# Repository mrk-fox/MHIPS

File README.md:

<h1 align="center">MHIPS</h1>
<div align="center">Modular Human Interface Panels System</div>
<br>
<div align="center">

</div>
<br>

<br> <br>
# Introduction
As controlling any type of craft with electronical components reqiring human intervention to function grows with the complexity of the craft and its tasks, I have decided to design a controlling system which is modular and uses near-aerospace-safety protocolls.

**Please pay attention to the fact that this project is still being developed. There is no "final solution" or such similar.**

## Functionality and goals

Every sucesfull project resembles a solution for a problem. Thus, the problem needs to be formulated before a solution is deigned. The problem that this project solves is the complexity of digital menus and the lack of haptic response in controlling anything with pure software.
My solution is a _modular, standartized panel system_ 
Hence, a ruleset was reqired to ensure the mulitcompatiability and extensiabiliy of this project.

### Why is it unique?
A central question in research, engineering and most other fields is "why has nobody done this before". Well, there are solutions to thes problem. Even one NASA provides in their GitHub repositories. But all of them are way to professional for amateur/non-professional use.

### Why did i make it?
Well, I'm planning on buiding an autonomous portable UAV someday. One day. Maybe. So these can be the GCC controls.

# Standartization

In this section we define a convention for the MHIPS (Modular Human Interface Panel System).
``` 
1. The abbreviation "MHIPS" stands for "Modular Human Interface Panel System".
      a. A panel is defined as a mounted and rigid resembly of multiple tiles, solving a user-defined task.
      b. A tile is defined as the smallest unit of the system. Any tile consists of the following components:
           b.1. A CAN-Capable read-write PCB as the BusPlate.
           b.2. A casing consisting of the front case and the backplate
           b.3. Input and output elements as Light Emitting Diodes, Buttons, Switches and more mounted into the front plate of the casing
      c. A rack is defined as the structure carrying and spacing the tiles.
2. The basic structure for a rack is a 5mm wide frame with the inner sizing of 50x50mm and a thickness of minimum 4mm. By fusing such frames togoether a rack is built. Each basic frame resembles the size of one unit (1U).
3. We define three levels of controll elements protection to ensure a dynamic range of application and environemntal adaptation.
      a. A level 3 tile is defined as a tile with no switch protection against accidental action.
      b. A level 2 tile is defined as a tile with sufficient control elements protection to ensure protection against accidental action. Only fully contacted switches (e.g.       ON-ON) are allowed.
      c. A level 1 tile is defined as a tile with maximal protection against accidental action. Double action is the minimum requirement. We split the level 1 category in the following subgroups:
            c.1. A level 1-S tile is definied as a tile meeting the basic level 1 requirements and the additional requirement of the maxiaml control element density of one control element per rack unit.
            c.2. A level 1-HV tile is definied as a tile meeting the basic level 1 requirements and additionally having the front tile face colored in a high visiability pattern (e.g. black and yellow stripes, 15mm wide at a 45° angle to the bottom plate of the tile) and having a maxiaml control element density of one control element per rack unit.
```
The given standartization is applied to all the racks and tiles in this current project.

# Example solution
In the following secion I will present my solution for the standartization and problem.

## BusPlate
The core piece of the work is the BusPlate resembling a PCB with the following features:

- RP2040 controller
- USB-C connectivity
- CAN Bus feature with MCP2515 controller
- Power and data over RJ45
- Decentralized computing capability on board

The following pictures are the front and back of the BusPlate PCB.

The following diagram shows the schematics for this PCB created in KiCad.

The following picures are the single PCB layers in the order "Front, In 1, In 2, Back"

## Assembly
Now, the assembly is rather simple and I remind the reader that he or she has a free will, but here are some guidelines to get through this, sometimes messy, process in calm.
1. Solder female jumper wires to the elements.
2. Insert the elements into the main tile casing
3. Screw the treaded rods into the main casing.
4. Connect the controller PCB to the jumper wires.
5. Insert the PCB onto the spacers with the treads in the mounting holes.
6. Place the backplate onto the assembly and secure the rods with nuts.

Such and assembled tile looks then this way:

Front

Back

### Firmware
The firmware is the current biggest point of potential advance. Currently, there is a simple programm implemented which is able to get user input from state cahnges and forward it per CAN to all boards. This is sufficient for a simple read system to control basic tasks.

## Credit
I thank this project to... <br>
... [KiCad](https://www.kicad.org/)<br>
... [HackClub Fallout](https://fallout.hackclub.com/)<br>
... [Autodesk Inventor](https://www.autodesk.com/de/products/inventor/overview)<br>

## License

This hardware project is licensed under the **CERN Open Hardware Licence v2 - Strongly Reciprocal (CERN-OHL-S)**.

See the [LICENSE](./LICENSE) file for details, or visit https://ohwr.org/cern_ohl_s_v2.

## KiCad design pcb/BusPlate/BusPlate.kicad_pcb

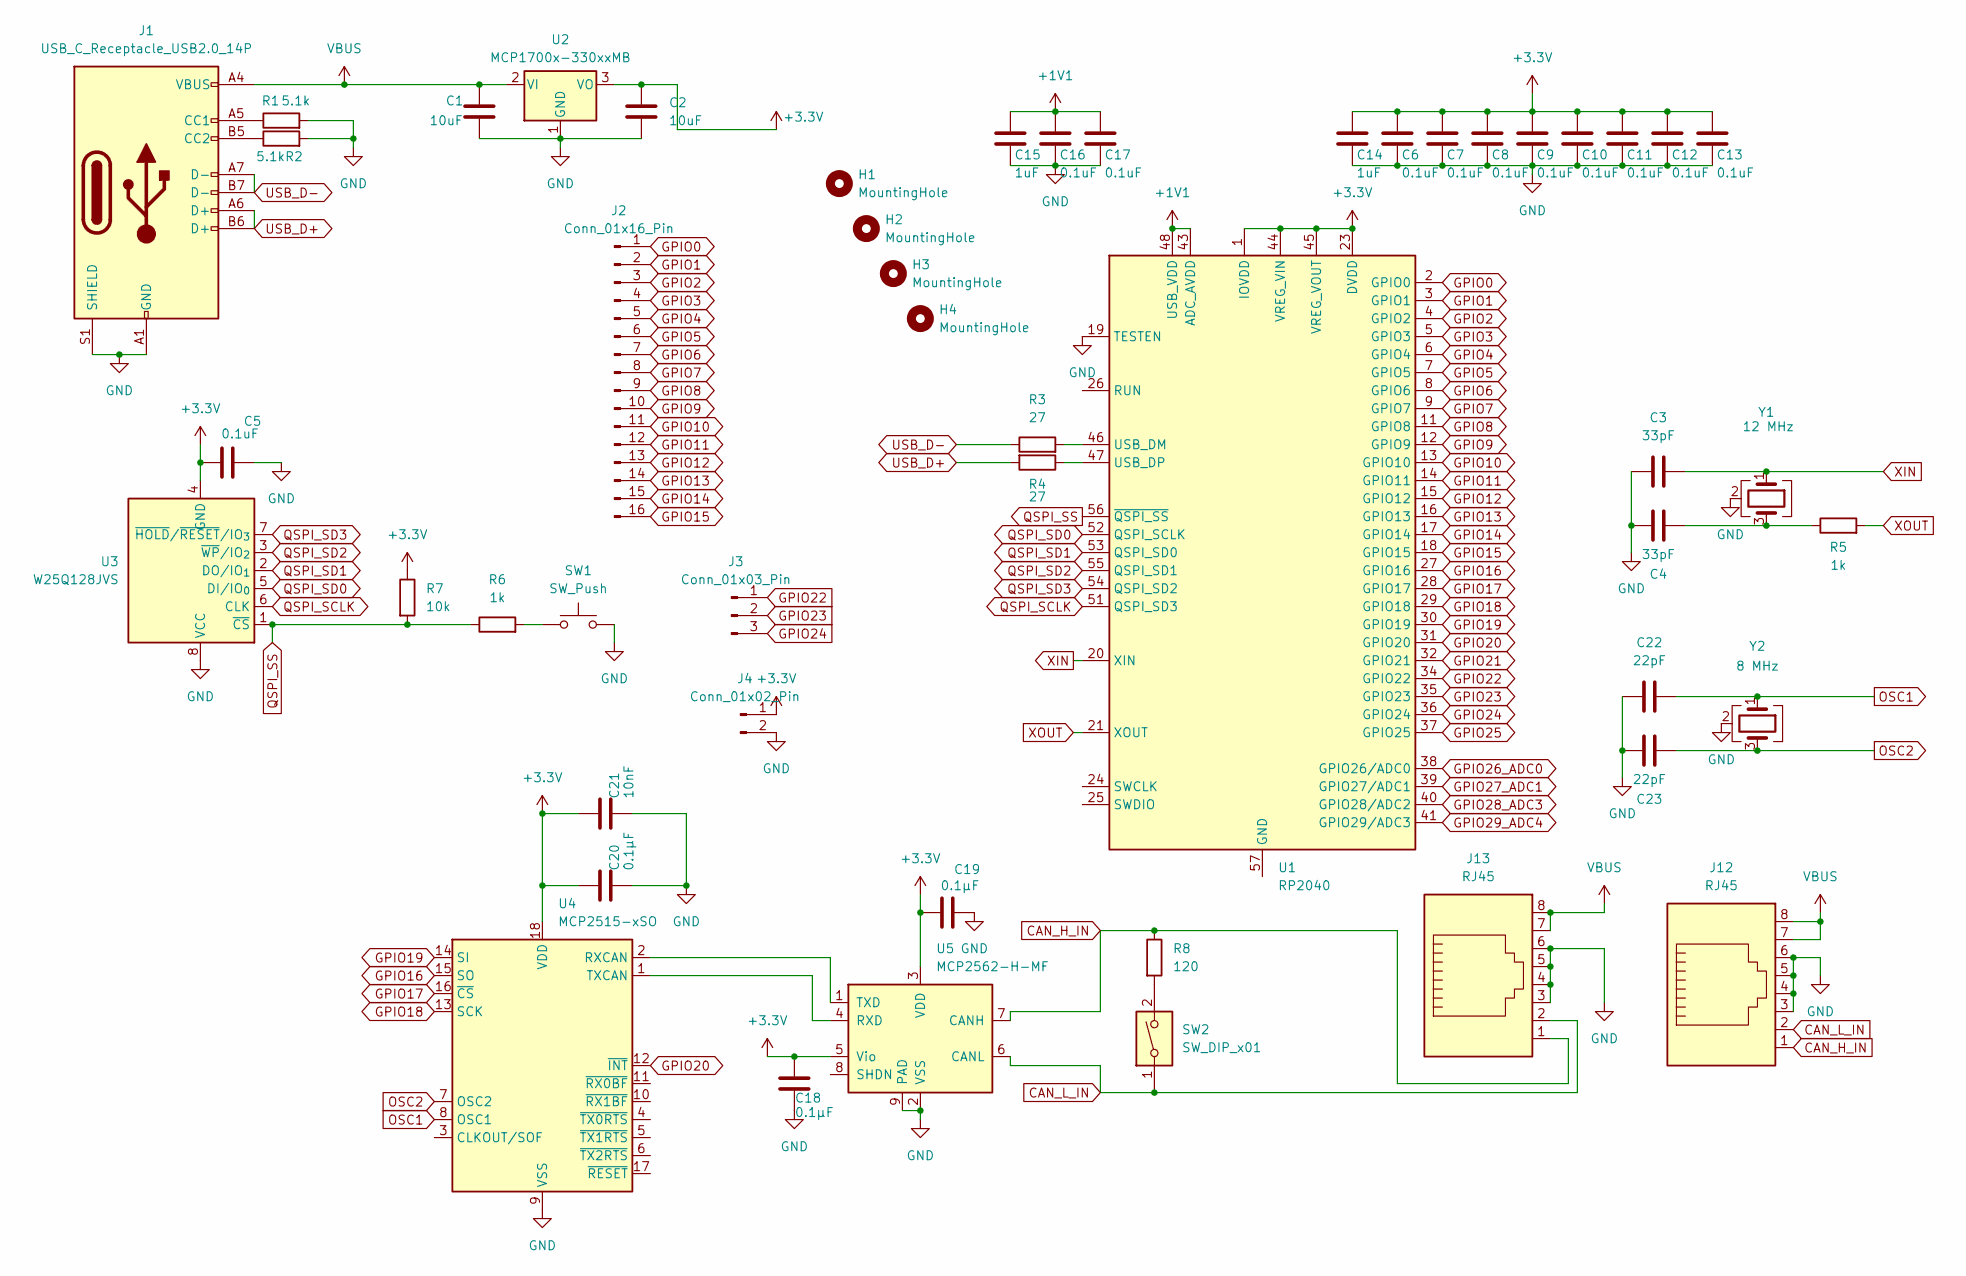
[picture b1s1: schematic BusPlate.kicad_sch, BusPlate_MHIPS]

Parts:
C1, C2: 10uF; C_0201_0603Metric
C3, C4: 33pF; C_0402_1005Metric
C5, C6, C7, C8, C9, C10, C11, C12, C13, C16, C17: 0.1uF; C_0402_1005Metric
C14, C15: 1uF; C_0402_1005Metric
C18, C19, C20: 0.1µF; C_0402_1005Metric
C21: 10nF; C_0402_1005Metric
C22, C23: 22pF; C_0402_1005Metric
H1, H2, H3, H4: MountingHole; MountingHole_2.2mm_M2
J1: USB_C_Receptacle_USB2.0_14P; USB_C_Receptacle_HRO_TYPE-C-31-M-12
J2: Conn_01x16_Pin; PinHeader_1x16_P2.54mm_Vertical
J3: Conn_01x03_Pin; PinHeader_1x03_P2.54mm_Vertical
J4: Conn_01x02_Pin; PinHeader_1x02_P2.54mm_Vertical
J12, J13: RJ45; RJ45_OST_PJ012-8P8CX_Vertical
R1, R2: 5.1k; R_0402_1005Metric
R3, R4: 27; R_0402_1005Metric
R5, R6: 1k; R_0402_1005Metric
R7: 10k; R_0402_1005Metric
R8: 120; R_0402_1005Metric
SW1: SW_Push; SW_Push_SPST_NO_Alps_SKRK
SW2: SW_DIP_x01; SW_DIP_SPSTx01_Slide_9.78x4.72mm_W7.62mm_P2.54mm
U1: RP2040; QFN-56-1EP_7x7mm_P0.4mm_EP3.2x3.2mm
U2: MCP1700x-330xxMB; SOT-89-3
U3: W25Q128JVS; SOIC-8_5.3x5.3mm_P1.27mm
U4: MCP2515-xSO; QFN-20-1EP_4x4mm_P0.5mm_EP2.5x2.5mm
U5: MCP2562-H-MF; DFN-8-1EP_3x3mm_P0.65mm_EP1.55x2.4mm
Y1: 12 MHz; Crystal_SMD_3225-4Pin_3.2x2.5mm
Y2: 8 MHz; Crystal_SMD_3225-4Pin_3.2x2.5mm

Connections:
+1V1: C15.1, C16.1, C17.1, U1.43 (ADC_AVDD), U1.48 (USB_VDD)
+3.3V: C2.1, C5.1, C6.1, C7.1, C8.1, C9.1, C10.1, C11.1, C12.1, C13.1, C14.1, C18.1, C19.1, C20.1, C21.1, J4.1, R7.1, U1.1 (IOVDD), U1.10 (IOVDD), U1.22 (IOVDD), U1.23 (DVDD), U1.33 (IOVDD), U1.42 (IOVDD), U1.44 (VREG_VIN), U1.45 (VREG_VOUT), U1.49 (IOVDD), U1.50 (DVDD), U2.3 (VO), U3.4 (GND), U4.18 (VDD), U5.3 (VDD), U5.5 (Vio)
CAN_H_IN: J12.1, J13.1, R8.1, U5.7 (CANH)
CAN_L_IN: J12.2, J13.2, SW2.1, U5.6 (CANL)
GND: C1.2, C2.2, C3.1, C4.2, C5.2, C6.2, C7.2, C8.2, C9.2, C10.2, C11.2, C12.2, C13.2, C14.2, C15.2, C16.2, C17.2, C18.2, C19.2, C20.2, C21.2, C22.1, C23.2, J1.A1 (GND), J1.A12 (GND), J1.B1 (GND), J1.B12 (GND), J1.S1 (SHIELD), J4.2, J12.3, J12.4, J12.5, J12.6, J13.3, J13.4, J13.5, J13.6, R1.2, R2.2, SW1.2, U1.19 (TESTEN), U2.1 (GND), U3.8 (VCC), U4.9 (VSS), U5.2 (VSS), U5.9 (PAD), Y1.2 (G), Y1.4 (G), Y2.2 (G), Y2.4 (G)
GPIO0: J2.1, U1.2 (GPIO0)
GPIO1: J2.2, U1.3 (GPIO1)
GPIO2: J2.3, U1.4 (GPIO2)
GPIO3: J2.4, U1.5 (GPIO3)
GPIO4: J2.5, U1.6 (GPIO4)
GPIO5: J2.6, U1.7 (GPIO5)
GPIO6: J2.7, U1.8 (GPIO6)
GPIO7: J2.8, U1.9 (GPIO7)
GPIO8: J2.9, U1.11 (GPIO8)
GPIO9: J2.10, U1.12 (GPIO9)
GPIO10: J2.11, U1.13 (GPIO10)
GPIO11: J2.12, U1.14 (GPIO11)
GPIO12: J2.13, U1.15 (GPIO12)
GPIO13: J2.14, U1.16 (GPIO13)
GPIO14: J2.15, U1.17 (GPIO14)
GPIO15: J2.16, U1.18 (GPIO15)
GPIO16: U1.27 (GPIO16), U4.15 (SO)
GPIO17: U1.28 (GPIO17), U4.16 (~CS)
GPIO18: U1.29 (GPIO18), U4.13 (SCK)
GPIO19: U1.30 (GPIO19), U4.14 (SI)
GPIO20: U1.31 (GPIO20), U4.12 (~INT)
GPIO21: U1.32 (GPIO21)
GPIO22: J3.1, U1.34 (GPIO22)
GPIO23: J3.2, U1.35 (GPIO23)
GPIO24: J3.3, U1.36 (GPIO24)
GPIO25: U1.37 (GPIO25)
GPIO26_ADC0: U1.38 (GPIO26/ADC0)
GPIO27_ADC1: U1.39 (GPIO27/ADC1)
GPIO28_ADC3: U1.40 (GPIO28/ADC2)
GPIO29_ADC4: U1.41 (GPIO29/ADC3)
unnamed: C4.1, R5.1, Y1.3
unnamed: J1.A5 (CC1), R1.1
unnamed: J1.B5 (CC2), R2.1
unnamed: R6.2, SW1.1
unnamed: R8.2, SW2.2
unnamed: R3.2, U1.46 (USB_DM)
unnamed: R4.1, U1.47 (USB_DP)
unnamed: U4.2 (RXCAN), U5.1 (TXD)
unnamed: U4.1 (TXCAN), U5.4 (RXD)
OSC1: C22.2, U4.8 (OSC1), Y2.1
OSC2: C23.1, U4.7 (OSC2), Y2.3
QSPI_SCLK: U1.51 (QSPI_SD3), U3.6 (CLK)
QSPI_SD0: U1.52 (QSPI_SCLK), U3.5 (DI/IO_{0})
QSPI_SD1: U1.53 (QSPI_SD0), U3.2 (DO/IO_{1})
QSPI_SD2: U1.55 (QSPI_SD1), U3.3 (~WP/IO_{2})
QSPI_SD3: U1.54 (QSPI_SD2), U3.7 (~HOLD/~RESET/IO_{3})
QSPI_SS: R6.1, R7.2, U1.56 (~QSPI_SS), U3.1 (~CS)
USB_D+: J1.A6 (D+), J1.B6 (D+), R4.2
USB_D-: J1.A7 (D-), J1.B7 (D-), R3.1
VBUS: C1.1, J1.A4 (VBUS), J1.A9 (VBUS), J1.B4 (VBUS), J1.B9 (VBUS), J12.7, J12.8, J13.7, J13.8, U2.2 (VI)
XIN: C3.2, U1.20 (XIN), Y1.1
XOUT: R5.2, U1.21 (XOUT)

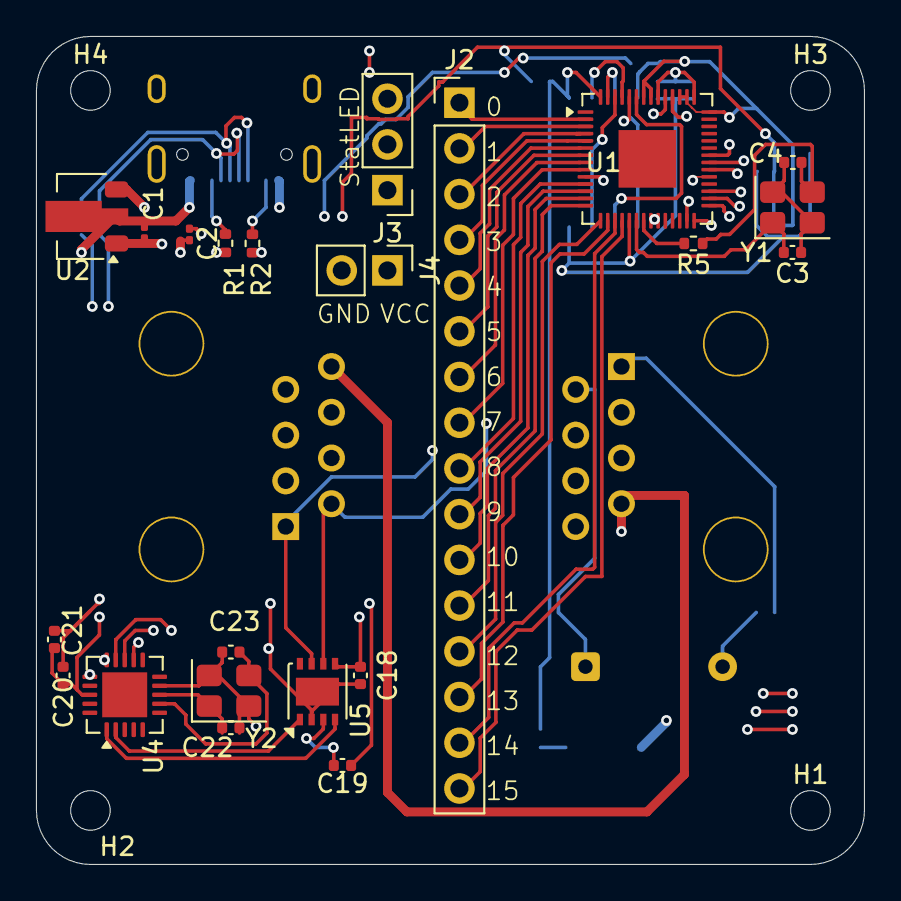
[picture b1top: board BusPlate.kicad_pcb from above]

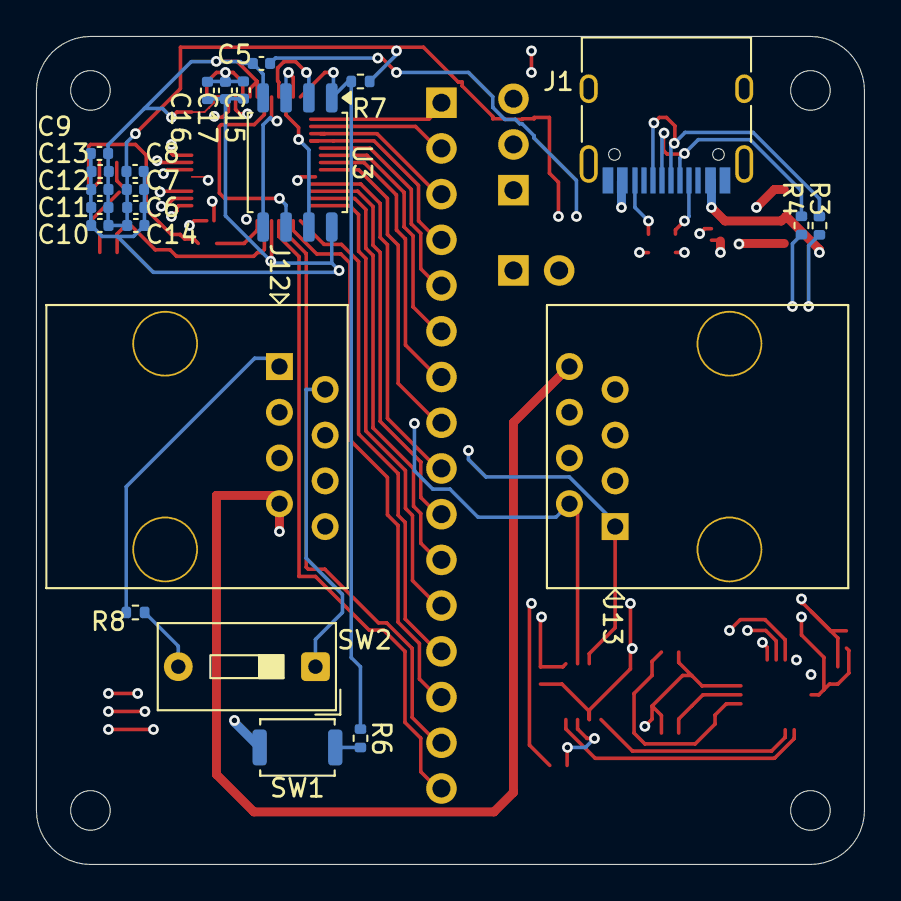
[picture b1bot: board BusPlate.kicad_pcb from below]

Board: 4 copper layers, 46.0 x 46.0 mm, 50 parts (24 on the bottom side), 51 nets.

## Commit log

2026-04-05 First PCB design completed, set rules for modularity
2026-04-05 Update project name to 'MHIPS' and add 'System'
2026-04-06 Ready first PCB
2026-04-07 Further rack and PCB development
2026-04-12 Add BusPlate models, update PCB & reorganize tiles
    Add a collection of BusPlate 3D/part models and a tile PNG, reorganize several model assemblies into lvl301x01_4t/OldVersions, and update switch model versioning. Adjust KiCad board files (BusPlate.k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
2026-05-08 Add PCB files, models, tiles, and BOM
    Add BOM.csv and multiple project assets: KiCad PCB and Gerber outputs for BusPlate (including backups and .zip), update BusPlate.kicad_pcb, and add example pictures. Add and reorganize numerous CAD m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
2026-05-09 Added firmware
2026-05-09 Fix image display and alignment in README
    Updated README to include an image with proper alignment and removed old image syntax.
2026-05-09 Enhance README with introduction and standards
    Added introduction and standardization sections to README.
2026-05-10 Add KiCad lockfile, update TODO and image
    Expanded TODO.txt with firmware notes and a basic setup/loop flow (define master/slave and addresses, init SPI/MCP and buttons, handle button presses and incoming data). Added pcb/BusPlate/~BusPlate.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
2026-05-10 Update README with detailed component definitions
    Expanded definitions for tiles, racks, and control levels. Added details about the BusPlate and included images of the PCB layers.
2026-05-10 Enhance README with project badges and new sections
    Added badges for KiCad, Espressif, and AutoDesk, and included sections on uniqueness and motivation for the project.
2026-05-10 Add backplate version, update backplate and image
    Add an OldVersions copy of the backplate IPT, replace/update the main backplate IPT binary, add a small example tile back PNG, and remove a transient KiCad PCB lock file. Housekeeping change to keep 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
2026-05-10 Update README with credits and license details
    Added credits and license information to the README.
2026-05-10 Added STEP files

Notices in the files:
README.md:
License: CERN-OHL-S
